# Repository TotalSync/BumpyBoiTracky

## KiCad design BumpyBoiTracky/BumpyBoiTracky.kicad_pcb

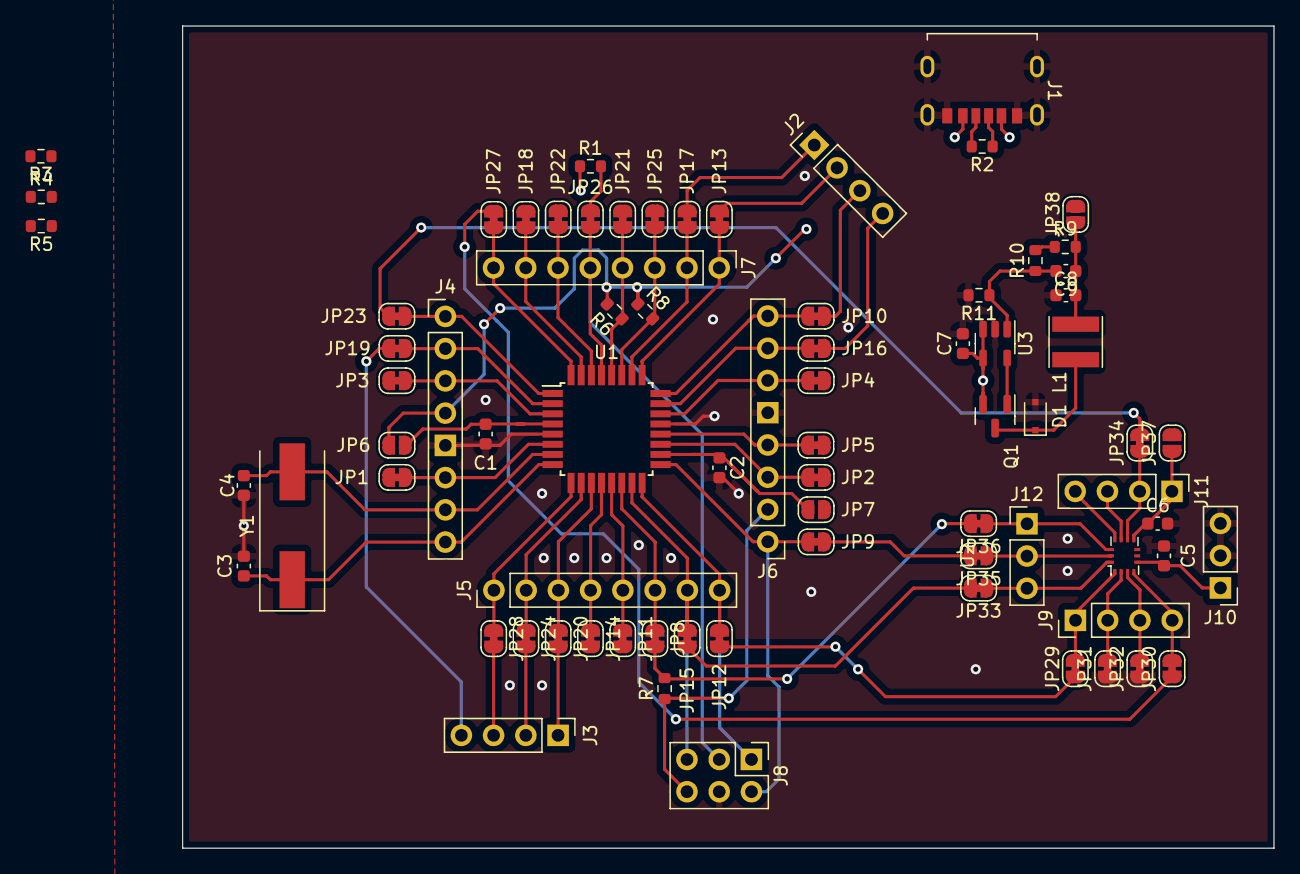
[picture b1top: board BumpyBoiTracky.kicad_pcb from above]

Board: 2 copper layers, 86.0 x 64.8 mm, 77 parts (0 on the bottom side), 68 nets.

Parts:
C1, C2: 1u; C_0603_1608Metric
C3, C4: 20p; C_0603_1608Metric
C5, C6: 100n; C_0603_1608Metric
C7: 10u; C_0603_1608Metric
C8: 100u; C_0603_1608Metric
C9: 1n; C_0603_1608Metric
D1: PMEG1020EJ,115; D_SOD-323F
J1: USB_C_Receptacle; Amphenol_USB-C_10164359-00011LF
J2, J3, J9, J11: Conn_01x04_Female; PinHeader_1x04_P2.54mm_Vertical
J4, J5, J6, J7: Conn_01x08_Female; PinHeader_1x08_P2.54mm_Vertical
J8: ICSP; PinHeader_2x03_P2.54mm_Vertical
J10, J12: Conn_01x03_Female; PinHeader_1x03_P2.54mm_Vertical
JP1, JP2, JP3, JP4, JP5, JP8, JP9, JP10, JP11, JP12, JP13, JP14, JP15, JP16, JP17, JP18, JP19, JP20, JP21, JP22, JP23, JP24, JP25, JP26, JP27, JP28, JP29, JP30, JP31, JP32, JP33, JP34, JP35, JP36: SolderJumper_2_Bridged; SolderJumper-2_P1.3mm_Bridged_RoundedPad1.0x1.5mm
JP6, JP7, JP37, JP38: SolderJumper_2_Open; SolderJumper-2_P1.3mm_Open_RoundedPad1.0x1.5mm
L1: 10u; L_Taiyo-Yuden_NR-40xx
Q1: Q_PMOS_GSD; SOT-23
R1, R4: 1.5k; R_0603_1608Metric
R2: 36k; R_0603_1608Metric
R3, R5: 15k; R_0603_1608Metric
R6, R7, R8, R11: 10k; R_0603_1608Metric
R9: 30k; R_0603_1608Metric
R10: 1k; R_0603_1608Metric
U1: ATmega328PB-A; TQFP-32_7x7mm_P0.8mm
U2: LSM6DSRX; LGA-14L
U3: LM3475; SOT-23-5
Y1: 8MHz; Crystal_SMD_HC49-SD

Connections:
+3.3V: JP37.2 (B), JP38.2 (B), R4.1
+5V: C7.1, J1.A9 (VBUS), J1.B9 (VBUS), J4.4, J6.2, J8.6, JP6.2 (B), JP7.2 (B), Q1.2 (S), R1.1, R6.1, R7.1, R8.1, U3.3 (EN), U3.4 (VIN)
/Controller/A0: J2.4, JP16.2 (B)
/Controller/A1: J2.3, JP10.2 (B)
/Controller/A2: J2.2, JP13.2 (B)
/Controller/A3: J2.1, JP17.2 (B)
/Controller/D0: J3.4, JP19.2 (B)
/Controller/D1: J3.3, JP28.2 (B)
/Controller/D2: J3.2, JP24.2 (B)
/Controller/D3: J3.1, JP20.2 (B)
/Controller/~RST: JP26.2 (B), R1.2
/INT1: JP27.2 (B), JP30.1 (A)
/INT2: JP23.2 (B), JP34.2 (B)
/MISO: JP12.2 (B), JP29.1 (A)
/MOSI: JP15.2 (B), JP33.2 (B)
/SCK: JP9.2 (B), JP35.2 (B)
/USB_CC1: J1.A5 (CC1), R2.1
/USB_CC2: J1.B5 (CC2), R2.2
/USB_D+: R4.2, R5.1
/~CS: JP8.2 (B), JP36.2 (B), R7.2
GND: C1.2, C2.2, C3.2, C4.2, C5.2, C6.2, C7.2, C8.2, D1.2 (A), J1.A12 (GND), J1.B12 (GND), J1.Earth, J4.5, J6.5, J8.4, J10.2, J10.3, JP31.1 (A), JP32.1 (A), R3.2, R5.2, R11.2, U1.5 (GND), U1.21 (GND), U2.6 (GND), U2.7 (GND), U3.2 (GND)
unnamed: C1.1, JP6.1 (A), U1.4 (VCC)
unnamed: C2.1, JP7.1 (A), U1.18 (AVCC)
unnamed: C3.1, J4.8, U1.8 (XTAL2/PB7), Y1.1
unnamed: C4.1, J4.7, U1.7 (XTAL1/PB6), Y1.2
unnamed: C5.1, J10.1, U2.5 (V_{DD_IO})
unnamed: C6.1, J11.1, JP37.1 (A), U2.8 (V_{DD})
unnamed: C8.1, C9.1, JP38.1 (A), L1.2, R9.2
unnamed: C9.2, R10.1, R11.1, U3.1 (FB)
unnamed: D1.1 (K), L1.1, Q1.3 (D)
unnamed: J4.1, JP23.1 (A), U1.1 (PD3)
unnamed: J4.2, JP19.1 (A), U1.2 (PD4)
unnamed: J4.3, JP3.2 (B), U1.3 (PE0)
unnamed: J4.6, JP1.2 (B), U1.6 (PE1)
unnamed: J5.1, JP28.1 (A), U1.9 (PD5)
unnamed: J5.2, JP24.1 (A), U1.10 (PD6)
unnamed: J5.3, JP20.1 (A), U1.11 (PD7)
unnamed: J5.4, JP14.1 (A), U1.12 (PB0)
unnamed: J5.5, JP11.1 (A), U1.13 (PB1)
unnamed: J5.6, JP8.1 (A), U1.14 (PB2)
unnamed: J5.7, J8.5, JP15.1 (A), U1.15 (PB3)
unnamed: J5.8, J8.1, JP12.1 (A), U1.16 (PB4)
unnamed: J6.1, J8.2, JP9.1 (A), U1.17 (PB5)
unnamed: J6.3, JP2.2 (B), U1.19 (PE2)
unnamed: J6.4, JP5.2 (B), U1.20 (AREF)
unnamed: J6.6, JP4.2 (B), U1.22 (PE3)
unnamed: J6.7, JP16.1 (A), U1.23 (PC0)
unnamed: J6.8, JP10.1 (A), U1.24 (PC1)
unnamed: J7.1, JP13.1 (A), U1.25 (PC2)
unnamed: J7.2, JP17.1 (A), U1.26 (PC3)
unnamed: J7.3, JP25.1 (A), R8.2, U1.27 (PC4)
unnamed: J7.4, JP21.1 (A), R6.2, U1.28 (PC5)
unnamed: J7.5, J8.3, JP26.1 (A), U1.29 (~RESET/PC6)
unnamed: J7.6, JP22.1 (A), U1.30 (PD0)
unnamed: J7.7, JP18.1 (A), U1.31 (PD1)
unnamed: J7.8, JP27.1 (A), U1.32 (PD2)
unnamed: J9.1, JP29.2 (B), U2.1 (SDO)
unnamed: J9.2, JP31.2 (B), U2.2 (SDx)
unnamed: J9.3, JP32.2 (B), U2.3 (SCx)
unnamed: J9.4, JP30.2 (B), U2.4 (INT1)
unnamed: J11.2, JP34.1 (A), U2.9 (INT2)
unnamed: J11.3, U2.10 (OCS_{Aux})
unnamed: J11.4, U2.11 (SDO_{Aux})
unnamed: J12.1, JP36.1 (A), U2.12 (CS)
unnamed: J12.2, JP35.1 (A), U2.13 (SCL)
unnamed: J12.3, JP33.1 (A), U2.14 (SDA)
unnamed: Q1.1 (G), U3.5 (PGATE)
unnamed: R9.1, R10.2

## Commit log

2023-03-25 Init
2023-03-25 Controller Added
    Added controller and Sensor. Begun work on prog interface
2023-05-26 Added Debug Hardware and finalized iteration design
2023-05-26 (adding forgotten files)
2023-05-27 Began layout for circuit board
